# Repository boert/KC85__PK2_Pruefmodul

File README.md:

# KC85__PK2_Pruefmodul
Nachentwickelte Leiterplatte zum Prüfmodul PK2 für den KC85/4 aus Mühlhausen.
Bisher ist der Leiterplattenentwurf nicht getestet worden (02/2026).

## Schaltplan

## Layout

## EPROMs
Ein EPROM enthält das Betriebssystem CAOS 4.2, das andere die 16 in der Anleitung beschriebenen Prüfprogramme.
Die Prüfsumme über den Speicherinhalt wird nach CRC-CCITT (CRC-16) [^1] berechnet:
```
$ jacksum -a crc:16,1021,ffff,false,false,0 -X *.BIN
79D5    8192    Pruefmodul_CAOS_42.BIN
3578    8192    Pruefmodul_P222.BIN
```

Vielen Dank an Andreas, Guido, KaiOr und Ralle für die Vorlagen!

[^1]: [Wikipedia, Zyklische Redundanzprüfung](https://de.wikipedia.org/wiki/Zyklische_Redundanzpr%C3%BCfung)

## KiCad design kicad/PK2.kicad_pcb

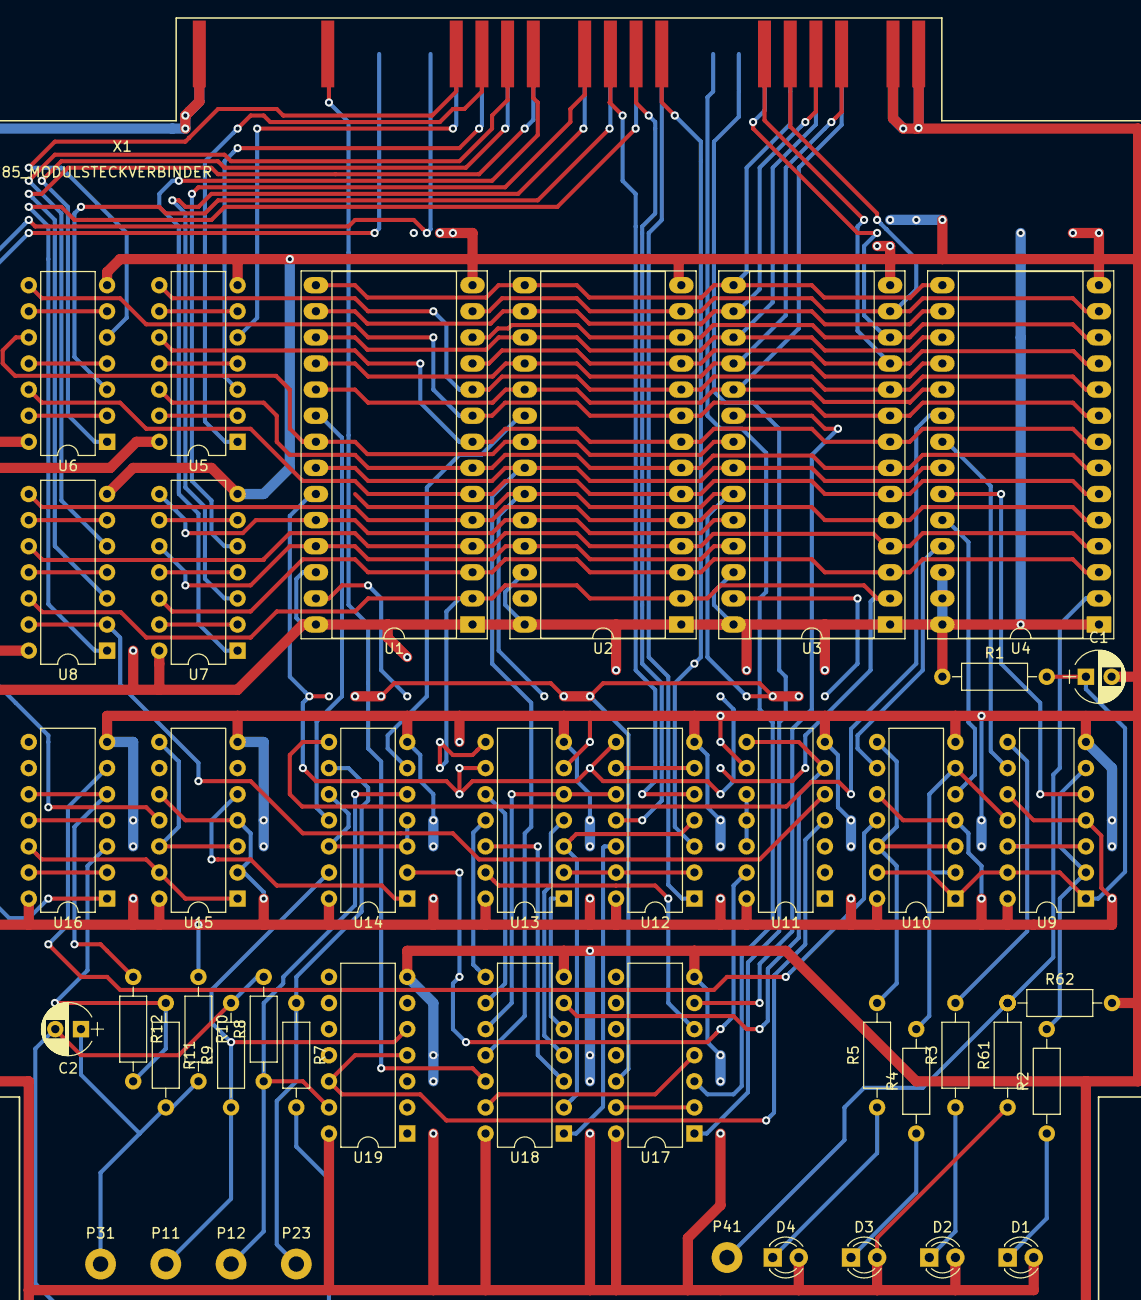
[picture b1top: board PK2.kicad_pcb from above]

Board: 2 copper layers, 44 parts (0 on the bottom side), 106 nets.

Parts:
C1, C2: 10µ; CP_Radial_D5.0mm_P2.50mm
D1, D2, D3, D4: LED; LED_D3.0mm
P11, P12, P23, P31, P41: TestPoint; Measurement_Point_Round-TH_Big
R1, R12: 2,2k; R_Axial_DIN0207_L6.3mm_D2.5mm_P10.16mm_Horizontal
R2, R3, R4, R5: 270; R_Axial_DIN0207_L6.3mm_D2.5mm_P10.16mm_Horizontal
R7, R9: 1k; R_Axial_DIN0207_L6.3mm_D2.5mm_P10.16mm_Horizontal
R8, R61, R62: n.b.; R_Axial_DIN0207_L6.3mm_D2.5mm_P10.16mm_Horizontal
R10: 4,7k; R_Axial_DIN0207_L6.3mm_D2.5mm_P10.16mm_Horizontal
R11: 22; R_Axial_DIN0207_L6.3mm_D2.5mm_P10.16mm_Horizontal
U1, U2, U3, U4: 27C256; DIP-28_W15.24mm_Socket_LongPads
U5, U6, U7, U8, U12, U16, U17: DL004; DIP-14_W7.62mm
U9, U10, U15: DL074; DIP-14_W7.62mm
U11: DL002 (n.b.); DIP-14_W7.62mm
U13, U19: DL002; DIP-14_W7.62mm
U14, U18: DL000; DIP-14_W7.62mm
X1: KC85_MODULSTECKVERBINDER; KC85_Modul

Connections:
/A8: U4.25, U10.9
/A9: U4.24, U10.5
/A10: U4.21, U9.9
/A11: U4.23, U9.5
/A12: P41.1, R61.2, R62.1, U4.2
/P23: P23.1, R7.1, U14.9
/P31: C2.1, P31.1, R10.2, R11.2
AB0: U5.5, X1.19A
AB0_: U1.10, U2.10, U3.10, U4.10, U5.8
AB1: U6.5, X1.19B
AB1_: U1.9, U2.9, U3.9, U4.9, U6.8
AB2: U5.3, X1.18A
AB2_: U1.8, U2.8, U3.8, U4.8, U5.10
AB3: U5.1, X1.18B
AB3_: U1.7, U2.7, U3.7, U4.7, U5.12
AB4: U6.1, X1.17A
AB4_: U1.6, U2.6, U3.6, U4.6, U6.12
AB5: U8.5, X1.17B
AB5_: U1.5, U2.5, U3.5, U4.5, U8.8
AB6: U8.3, X1.16A
AB6_: U1.4, U2.4, U3.4, U4.4, U8.10
AB7: U7.1, X1.16B
AB7_: U1.3, U2.3, U3.3, U4.3, U7.12
AB8: U7.3, X1.14A
AB8_: U1.25, U2.25, U3.25, U7.10
AB9: U7.5, X1.14B
AB9_: U1.24, U2.24, U3.24, U7.8
AB10: U6.3, X1.13A
AB10_: U1.21, U2.21, U3.21, U6.10
AB11: U12.5, X1.13B
AB11_: U1.23, U12.8, U13.9
AB12: U8.1, X1.12A
AB12_: U1.2, U2.2, U3.2, U8.12, U13.8
AB13: U12.11, X1.12B
AB14: U12.1, X1.11A
AB14_: U12.12, U18.1
AB15: U12.3, X1.11B
DB0: U1.11, U2.11, U3.11, U4.11, X1.7B
DB1: U1.12, U2.12, U3.12, U4.12, X1.7A
DB2: U1.13, U2.13, U3.13, U4.13, X1.6B
DB3: U1.15, U2.15, U3.15, U4.15, X1.6A
DB4: U1.16, U2.16, U3.16, U4.16, X1.5B
DB5: U1.17, U2.17, U3.17, U4.17, X1.5A
DB6: U1.18, U2.18, U3.18, U4.18, X1.4B
DB7: U1.19, U2.19, U3.19, U4.19, X1.4A
GND: C1.2, C2.2, R7.2, R8.2, R9.2, R62.2, U1.14, U2.14, U3.14, U4.14, U5.7, U6.7, U7.7, U8.7, U9.7, U10.7, U11.7, U11.9, U12.7, U13.6, U13.7, U14.7, U15.7, U16.7, U17.7, U18.7, U19.7, X1.1A, X1.1B, X1.2A, X1.2B
MEI: U18.12, X1.24B
MREQ_: U17.4, U18.13
unnamed: C1.1, R1.2, U9.1, U9.13, U10.1, U10.13
unnamed: D1.1, R2.1
unnamed: D2.1, R3.1
unnamed: D3.1, R4.1
unnamed: D4.1, R5.1
unnamed: R2.2, U9.2, U9.6
unnamed: R3.2, U9.3, U9.8, U9.12
unnamed: R4.2, U9.11, U10.2, U10.6
unnamed: R5.2, U10.3, U10.8, U10.12
unnamed: R11.1, R12.2, U16.3
unnamed: R12.1, U16.5, U16.10
unnamed: U5.6, U5.9
unnamed: U5.4, U5.11
unnamed: U5.2, U5.13
unnamed: U6.6, U6.9
unnamed: U6.4, U6.11
unnamed: U6.2, U6.13
unnamed: U7.6, U7.9
unnamed: U7.4, U7.11
unnamed: U7.2, U7.13
unnamed: U8.6, U8.9
unnamed: U8.4, U8.11
unnamed: U10.11, U16.6
unnamed: U11.4, U19.4, U19.12
unnamed: U11.6, U11.8, U18.6
unnamed: U11.10, U11.11, U11.12
unnamed: U11.13, U14.2
unnamed: U12.6, U12.9
unnamed: U13.1, U18.5
unnamed: U13.4, U18.4
unnamed: U13.10, U18.9
unnamed: U13.11, U18.8
unnamed: U13.12, U18.3
unnamed: U13.13, U17.5
unnamed: U14.1, U15.5
unnamed: U14.3, U14.4, U14.10, U14.12
unnamed: U15.3, U15.8, U15.12
unnamed: U16.4, U16.11
unnamed: U16.2, U16.13
unnamed: U17.2, U17.13
P11: P11.1, R9.1, U14.13, U19.5
P12: P12.1, R8.1, U14.5, U19.13
VCC: D1.2, D2.2, D3.2, D4.2, R1.1, R10.1, R61.1, U1.1, U1.26, U1.27, U1.28, U2.1, U2.26, U2.28, U3.1, U3.26, U3.28, U4.1, U4.26, U4.27, U4.28, U5.14, U6.14, U7.14, U8.14, U9.4, U9.10, U9.14, U10.4, U10.10, U10.14, U11.14, U12.14, U13.14, U14.14, U15.2, U15.4, U15.10, U15.14, U16.14, U17.14, U18.14, U19.14, X1.29A, X1.29B
~AB12: U8.2, U8.13, U11.5
~AB13: U12.10, U13.5, U18.10
~AB14: U12.2, U12.13, U13.2
~AB15: U12.4, U13.3, U18.2
~M1: U15.11, X1.22A
~MREQ: U17.3, X1.9A
~OE: U1.22, U2.22, U3.22, U4.22, U18.11
~RESET: U16.1, X1.20A
~RESET_: U15.1, U15.13, U16.12
~U1_CE: U1.20, U14.11
~U2_CE: U2.20, U14.6
~U3_CE: U3.20, U17.6
~U4_CE: U4.20, U14.8
~WR: U17.1, X1.8A
~WR_: U2.23, U3.23, U17.12

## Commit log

2026-03-03 add files
2026-03-12 EPROMs ergänzt
2026-03-14 kompletten Quelltext ergänzt
2026-03-15 spearate Prüfprogramme ergänzt
